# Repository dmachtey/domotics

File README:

-*- mode: org -*-

* This is another domotics project
    - it is based on Beaglebone Black
    - Its able to control up to 64 Inputs or Outputs in blocks of 4
    - I've developed a main board were is possible to plug up to 16
      4-inputs or 4-outputs boards (4 GPIOs). All of them are
      optocoupled.
      - I've already developed a 4-relays board and 4-transistors
        board wich can control lights intensity by PWM and also
        4-imputs board
    - The power board can be connected to a battery and detect a mains
      failure
    - It's already able to comunicate with Openhab, an android and ios
      application
    - It's in production now since April 8th 2016 in my home
    - There is also 2 more slots with 3 and 4 analogs inputs, I'm
      planing to sense the battery level and natural light level.
    - Into one of the 16 slots I'm planing to connect some DS18B20 (up
      to 10 can be connected to one gpio) to sense the rooms
      temperatures.

* This is my first project to be published
  I'm trying to sort thins out to make them easier to understan

  I will re-write some of c++ objects to make them clear to understand

* This is what is now running
  - A full functional project is in production at my home have a look
    at the pictures folder
  - Now I'm controlling 5 PWM circuits for lights
  - I've also 5 inputs
  - All outputs are controlled by Openhab web application from LAN/WAN

* How to test this project
  - Get a Beagle bone black with Linux running
  - do :: apt-get install build-essential
  - do :: apt-get install linux-image-3.8.13-bone68 device-tree-compiler
    - to be able to compile new capes, they are needed to manage GPIOs
  - compile the cape /domotics/capes/half-in-half-pru.dts
    - copy the compiled code to /lib/firmware/
  - get yours electronics ready and connected to one of the gpio used
    on "on-production/test-pwm.cpp" like "GPIO 27"
  - Connect and input switch at "GPIO 4"
  - copy the contemns of "/domotics/on-production" to /pru2 at BBB
  - run /pru2/start.sh
  - Your led should get PWM controlled with the switch

  - Optional:
    If you want to run it with openhab for remote controll
    - Install libc-ares-dev uuid-dev libwrap0-dev libssl-dev needed by
      mosquitto library
    - Install mosquitto it can be downloaded here: http://mosquitto.org/download/
  - Install openhab, instructions at it's site: http://openhab.org/
    - copy /domotics/root/* to "/" at BBB
  - Install an configure your openhab to point to your BBB ip as http://BBBip:8080

* Project files
  - /domotics/docs/files-strucure.org

* Contact information
  - Damian Machtey
  - dmachtey at gmail com

* License
  The code and hardware is being released under GPL v3.

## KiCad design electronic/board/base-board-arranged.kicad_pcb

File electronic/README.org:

*Use kitcad to open the files*

* files structure and comments (should be here)

* Scripts/other programs
  - headers-cloner.py :: was used to automatically arrange the socket
       connectors
  - FreeRouting :: was used to help ruting
    - http://www.freerouting.net/fen/viewtopic.php?f=4&t=255

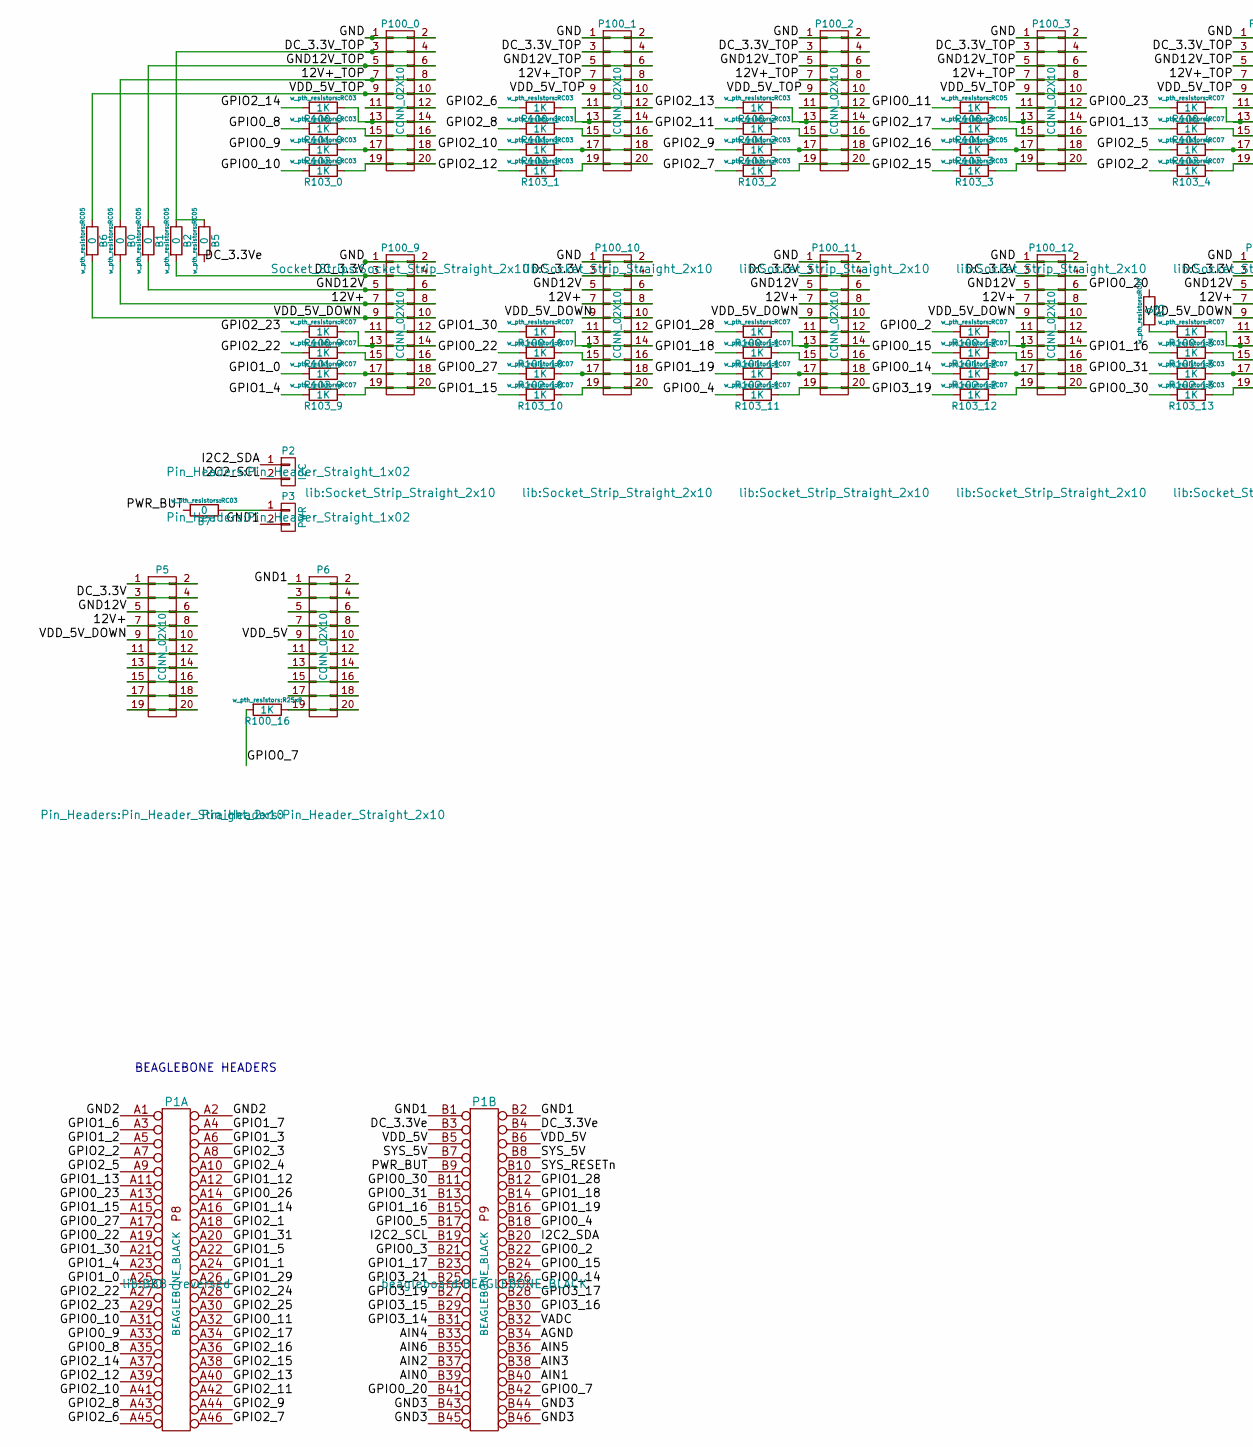
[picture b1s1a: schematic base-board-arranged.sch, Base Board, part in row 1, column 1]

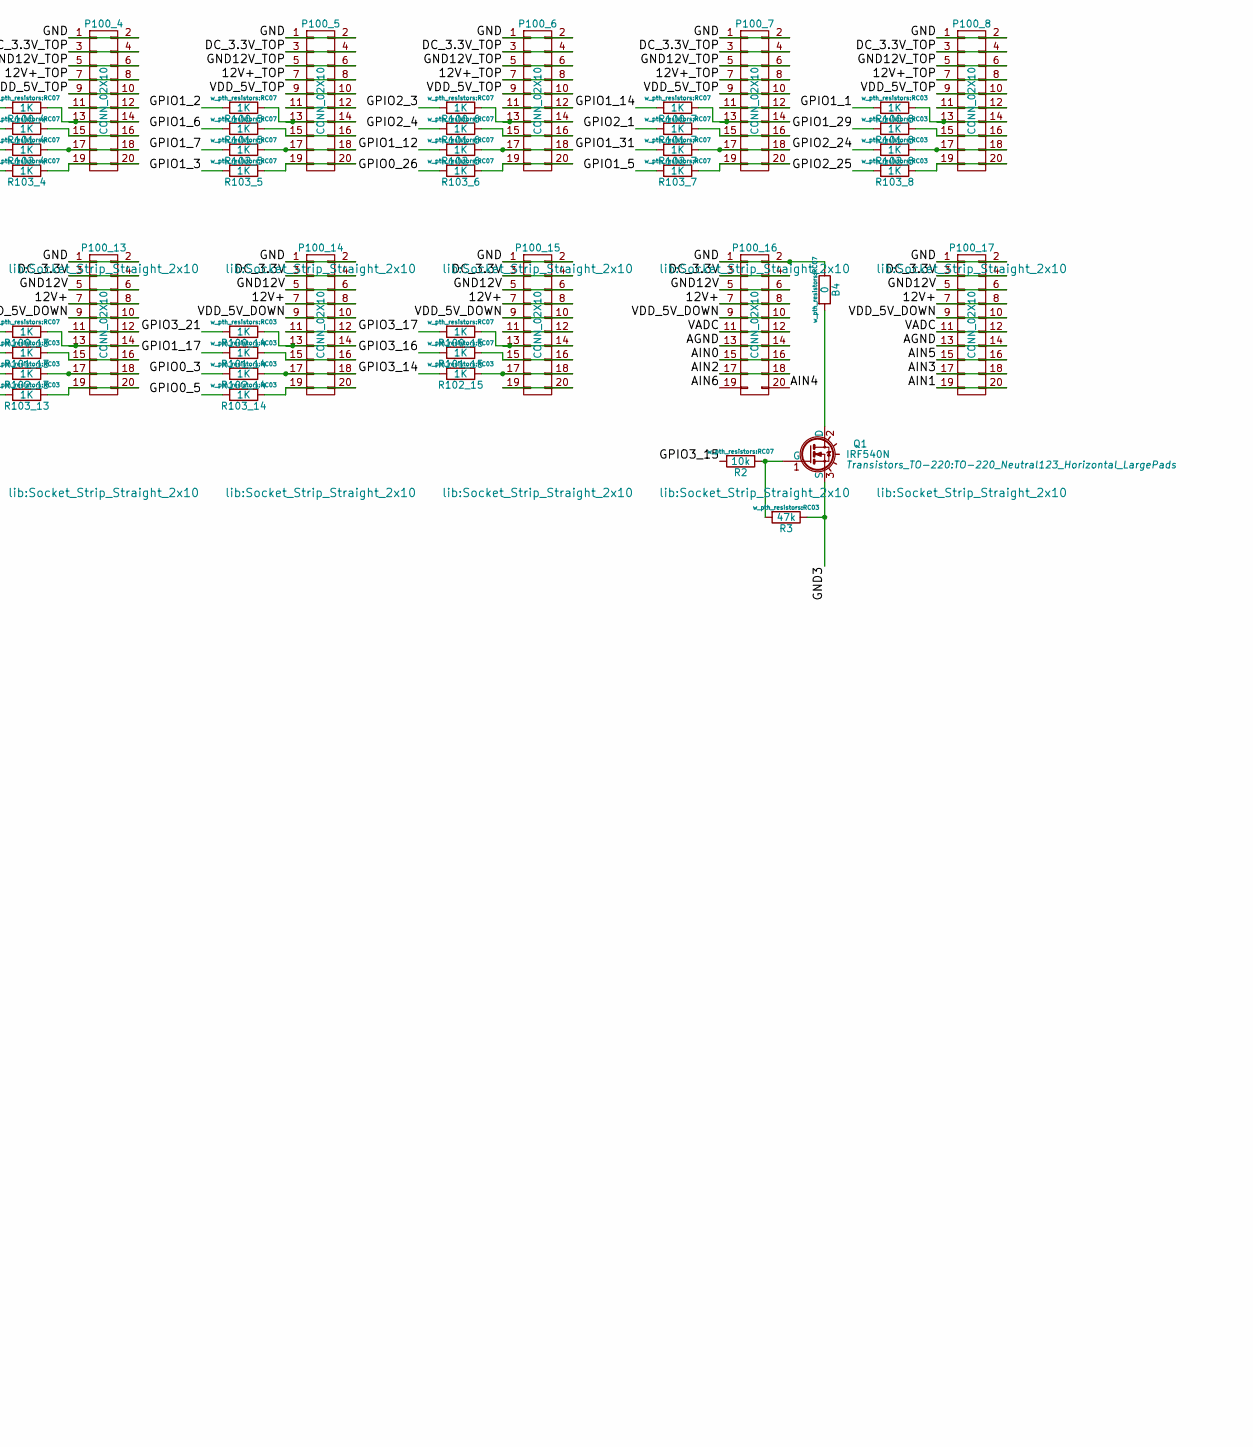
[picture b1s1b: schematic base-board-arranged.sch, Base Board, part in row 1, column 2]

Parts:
B0, B1, B2, B5, B6: 0; RC05
B3, B4: 0; RC07
B7: 0; RC03
P1: BEAGLEBONE_BLACK; BBB-reversed
P2: I2C; Pin_Header_Straight_1x02
P3: PWR; Pin_Header_Straight_1x02
P5, P6: CONN_02X10; Pin_Header_Straight_2x10
P100_0, P100_1, P100_2, P100_3, P100_4, P100_5, P100_6, P100_7, P100_8, P100_9, P100_10, P100_11, P100_12, P100_13, P100_14, P100_15, P100_16, P100_17: CONN_02X10; Socket_Strip_Straight_2x10
Q1: IRF540N; TO-220_Neutral123_Horizontal_LargePads
R2: 10k; RC07
R3: 47k; RC03
R100_0, R100_1, R100_2, R100_8, R100_14, R101_0, R101_1, R101_2, R101_8, R101_13, R101_14, R102_0, R102_1, R102_2, R102_8, R102_13, R102_14, R102_15, R103_0, R103_1, R103_2, R103_3, R103_8, R103_13, R103_14: 1K; RC03
R100_3, R101_3, R102_3: 1K; RC05
R100_4, R100_5, R100_6, R100_7, R100_9, R100_10, R100_11, R100_12, R100_13, R100_15, R101_4, R101_5, R101_6, R101_7, R101_9, R101_10, R101_11, R101_12, R101_15, R102_4, R102_5, R102_6, R102_7, R102_9, R102_10, R102_11, R102_12, R103_4, R103_5, R103_6, R103_7, R103_9, R103_10, R103_11, R103_12: 1K; RC07
R100_16: 1K; R25x8

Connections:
/12V+: B0.2, P5.7, P5.8, P100_9.7, P100_9.8, P100_10.7, P100_10.8, P100_11.7, P100_11.8, P100_12.7, P100_12.8, P100_13.7, P100_13.8, P100_14.7, P100_14.8, P100_15.7, P100_15.8, P100_16.7, P100_16.8, P100_17.7, P100_17.8
/12V+_TOP: B0.1, P100_0.7, P100_0.8, P100_1.7, P100_1.8, P100_2.7, P100_2.8, P100_3.7, P100_3.8, P100_4.7, P100_4.8, P100_5.7, P100_5.8, P100_6.7, P100_6.8, P100_7.7, P100_7.8, P100_8.7, P100_8.8
/AGND: P1.B34 (P34), P100_16.13, P100_16.14, P100_17.13, P100_17.14
/AIN0: P1.B39 (P39), P100_16.15, P100_16.16
/AIN1: P1.B40 (P40), P100_17.19, P100_17.20
/AIN2: P1.B37 (P37), P100_16.17, P100_16.18
/AIN3: P1.B38 (P38), P100_17.17, P100_17.18
/AIN4: P1.B33 (P33), P100_16.20
/AIN5: P1.B36 (P36), P100_17.15, P100_17.16
/AIN6: P1.B35 (P35), P100_16.19
/DC_3.3V: B2.2, P5.3, P5.4, P100_9.3, P100_9.4, P100_10.3, P100_10.4, P100_11.3, P100_11.4, P100_12.3, P100_12.4, P100_13.3, P100_13.4, P100_14.3, P100_14.4, P100_15.3, P100_15.4, P100_16.3, P100_16.4, P100_17.3, P100_17.4
/DC_3.3V_TOP: B2.1, B5.1, P100_0.3, P100_0.4, P100_1.3, P100_1.4, P100_2.3, P100_2.4, P100_3.3, P100_3.4, P100_4.3, P100_4.4, P100_5.3, P100_5.4, P100_6.3, P100_6.4, P100_7.3, P100_7.4, P100_8.3, P100_8.4
/DC_3.3Ve: B5.2, P1.B3, P1.B4 (P4)
/GND: B4.1, P100_0.1, P100_0.2, P100_1.1, P100_1.2, P100_2.1, P100_2.2, P100_3.1, P100_3.2, P100_4.1, P100_4.2, P100_5.1, P100_5.2, P100_6.1, P100_6.2, P100_7.1, P100_7.2, P100_8.1, P100_8.2, P100_9.1, P100_9.2, P100_10.1, P100_10.2, P100_11.1, P100_11.2, P100_12.1, P100_12.2, P100_13.1, P100_13.2, P100_14.1, P100_14.2, P100_15.1, P100_15.2, P100_16.1, P100_16.2, P100_17.1, P100_17.2
/GND1: P1.B1 (GND), P1.B2 (P2), P3.2, P6.1, P6.2
/GND2: P1.A1 (GND), P1.A2 (P2)
/GND3: P1.B43 (P43), P1.B44 (P44), P1.B45 (P45), P1.B46 (P46), Q1.3 (S), R3.1
/GND12V: B1.2, P5.5, P5.6, P100_9.5, P100_9.6, P100_10.5, P100_10.6, P100_11.5, P100_11.6, P100_12.5, P100_12.6, P100_13.5, P100_13.6, P100_14.5, P100_14.6, P100_15.5, P100_15.6, P100_16.5, P100_16.6, P100_17.5, P100_17.6
/GND12V_TOP: B1.1, P100_0.5, P100_0.6, P100_1.5, P100_1.6, P100_2.5, P100_2.6, P100_3.5, P100_3.6, P100_4.5, P100_4.6, P100_5.5, P100_5.6, P100_6.5, P100_6.6, P100_7.5, P100_7.6, P100_8.5, P100_8.6
/GPIO0_2: P1.B22 (P22), R100_12.2
/GPIO0_3: P1.B21 (P21), R102_14.2
/GPIO0_4: P1.B18 (P18), R103_11.2
/GPIO0_5: P1.B17 (P17), R103_14.2
/GPIO0_7: P1.B42 (P42), R100_16.2
/GPIO0_8: P1.A35 (P35), R101_0.2
/GPIO0_9: P1.A33 (P33), R102_0.2
/GPIO0_10: P1.A31 (P31), R103_0.2
/GPIO0_11: P1.A32 (P32), R100_3.2
/GPIO0_14: P1.B26 (P26), R102_12.2
/GPIO0_15: P1.B24 (P24), R101_12.2
/GPIO0_20: B3.1, P1.B41 (P41)
/GPIO0_22: P1.A19 (P19), R101_10.2
/GPIO0_23: P1.A13 (P13), R100_4.2
/GPIO0_26: P1.A14 (P14), R103_6.2
/GPIO0_27: P1.A17 (P17), R102_10.2
/GPIO0_30: P1.B11, R103_13.2
/GPIO0_31: P1.B13 (P13), R102_13.2
/GPIO1_0: P1.A25 (P25), R102_9.2
/GPIO1_1: P1.A24 (P24), R100_8.2
/GPIO1_2: P1.A5 (P5), R100_5.2
/GPIO1_3: P1.A6 (P6), R103_5.2
/GPIO1_4: P1.A23 (P23), R103_9.2
/GPIO1_5: P1.A22 (P22), R103_7.2
/GPIO1_6: P1.A3 (P3), R101_5.2
/GPIO1_7: P1.A4 (P4), R102_5.2
/GPIO1_12: P1.A12 (P12), R102_6.2
/GPIO1_13: P1.A11 (P11), R101_4.2
/GPIO1_14: P1.A16 (P16), R100_7.2
/GPIO1_15: P1.A15 (P15), R103_10.2
/GPIO1_16: P1.B15 (P15), R101_13.2
/GPIO1_17: P1.B23 (P23), R101_14.2
/GPIO1_18: P1.B14 (P14), R101_11.2
/GPIO1_19: P1.B16 (P16), R102_11.2
/GPIO1_28: P1.B12 (P12), R100_11.2
/GPIO1_29: P1.A26 (P26), R101_8.2
/GPIO1_30: P1.A21 (P21), R100_10.2
/GPIO1_31: P1.A20 (P20), R102_7.2
/GPIO2_1: P1.A18 (P18), R101_7.2
/GPIO2_2: P1.A7 (P7), R103_4.2
/GPIO2_3: P1.A8 (P8), R100_6.2
/GPIO2_4: P1.A10 (P10), R101_6.2
/GPIO2_5: P1.A9 (P9), R102_4.2
/GPIO2_6: P1.A45 (P45), R100_1.2
/GPIO2_7: P1.A46 (P46), R103_2.2
/GPIO2_8: P1.A43 (P43), R101_1.2
/GPIO2_9: P1.A44 (P44), R102_2.2
/GPIO2_10: P1.A41 (P41), R102_1.2
/GPIO2_11: P1.A42 (P42), R101_2.2
/GPIO2_12: P1.A39 (P39), R103_1.2
/GPIO2_13: P1.A40 (P40), R100_2.2
/GPIO2_14: P1.A37 (P37), R100_0.2
/GPIO2_15: P1.A38 (P38), R103_3.2
/GPIO2_16: P1.A36 (P36), R102_3.2
/GPIO2_17: P1.A34 (P34), R101_3.2
/GPIO2_22: P1.A27 (P27), R101_9.2
/GPIO2_23: P1.A29 (P29), R100_9.2
/GPIO2_24: P1.A28 (AP28), R102_8.2
/GPIO2_25: P1.A30 (P30), R103_8.2
/GPIO3_14: P1.B31 (P31), R102_15.2
/GPIO3_15: P1.B29 (P29), R2.2
/GPIO3_16: P1.B30 (P30), R101_15.2
/GPIO3_17: P1.B28 (AP28), R100_15.2
/GPIO3_19: P1.B27 (P27), R103_12.2
/GPIO3_21: P1.B25 (P25), R100_14.2
/I2C2_SCL: P1.B19 (P19), P2.2
/I2C2_SDA: P1.B20 (P20), P2.1
/PWR_BUT: B7.2, P1.B9 (P9)
/SYS_5V: P1.B7 (P7), P1.B8 (P8)
/SYS_RESETn: P1.B10 (P10)
/VADC: P1.B32 (P32), P100_16.11, P100_16.12, P100_17.11, P100_17.12
/VDD_5V: P1.B5 (P5), P1.B6 (P6), P6.9, P6.10
/VDD_5V_DOWN: B6.2, P5.9, P5.10, P100_9.9, P100_9.10, P100_10.9, P100_10.10, P100_11.9, P100_11.10, P100_12.9, P100_12.10, P100_13.9, P100_13.10, P100_14.9, P100_14.10, P100_15.9, P100_15.10, P100_16.9, P100_16.10, P100_17.9, P100_17.10
/VDD_5V_TOP: B6.1, P100_0.9, P100_0.10, P100_1.9, P100_1.10, P100_2.9, P100_2.10, P100_3.9, P100_3.10, P100_4.9, P100_4.10, P100_5.9, P100_5.10, P100_6.9, P100_6.10, P100_7.9, P100_7.10, P100_8.9, P100_8.10
unnamed: B3.2, R100_13.2
unnamed: B4.2, Q1.2 (D)
unnamed: B7.1, P3.1
unnamed: P5.1, P5.2
unnamed: P5.11, P5.12
unnamed: P5.13, P5.14
unnamed: P5.15, P5.16
unnamed: P5.17, P5.18
unnamed: P5.19, P5.20
unnamed: P6.3, P6.4
unnamed: P6.5, P6.6
unnamed: P6.7, P6.8
unnamed: P6.11, P6.12
unnamed: P6.13, P6.14
unnamed: P6.15, P6.16
unnamed: P6.17, P6.18
unnamed: P6.19, P6.20, R100_16.1
unnamed: P100_0.11, P100_0.12
unnamed: P100_0.13, P100_0.14, R100_0.1
unnamed: P100_0.15, P100_0.16, R101_0.1
unnamed: P100_0.17, P100_0.18, R102_0.1
unnamed: P100_0.19, P100_0.20, R103_0.1
unnamed: P100_1.11, P100_1.12
unnamed: P100_1.13, P100_1.14, R100_1.1
unnamed: P100_1.15, P100_1.16, R101_1.1
unnamed: P100_1.17, P100_1.18, R102_1.1
unnamed: P100_1.19, P100_1.20, R103_1.1
unnamed: P100_2.11, P100_2.12
unnamed: P100_2.13, P100_2.14, R100_2.1
unnamed: P100_2.15, P100_2.16, R101_2.1
unnamed: P100_2.17, P100_2.18, R102_2.1
unnamed: P100_2.19, P100_2.20, R103_2.1
unnamed: P100_3.11, P100_3.12
unnamed: P100_3.13, P100_3.14, R100_3.1
unnamed: P100_3.15, P100_3.16, R101_3.1
unnamed: P100_3.17, P100_3.18, R102_3.1
unnamed: P100_3.19, P100_3.20, R103_3.1
unnamed: P100_4.11, P100_4.12
unnamed: P100_4.13, P100_4.14, R100_4.1
unnamed: P100_4.15, P100_4.16, R101_4.1
unnamed: P100_4.17, P100_4.18, R102_4.1
unnamed: P100_4.19, P100_4.20, R103_4.1
unnamed: P100_5.11, P100_5.12
unnamed: P100_5.13, P100_5.14, R100_5.1
unnamed: P100_5.15, P100_5.16, R101_5.1
unnamed: P100_5.17, P100_5.18, R102_5.1
unnamed: P100_5.19, P100_5.20, R103_5.1
unnamed: P100_6.11, P100_6.12
unnamed: P100_6.13, P100_6.14, R100_6.1
unnamed: P100_6.15, P100_6.16, R101_6.1
unnamed: P100_6.17, P100_6.18, R102_6.1
unnamed: P100_6.19, P100_6.20, R103_6.1
unnamed: P100_7.11, P100_7.12
unnamed: P100_7.13, P100_7.14, R100_7.1
unnamed: P100_7.15, P100_7.16, R101_7.1
unnamed: P100_7.17, P100_7.18, R102_7.1
unnamed: P100_7.19, P100_7.20, R103_7.1
unnamed: P100_8.11, P100_8.12
unnamed: P100_8.13, P100_8.14, R100_8.1
unnamed: P100_8.15, P100_8.16, R101_8.1
unnamed: P100_8.17, P100_8.18, R102_8.1
unnamed: P100_8.19, P100_8.20, R103_8.1
unnamed: P100_9.11, P100_9.12
unnamed: P100_9.13, P100_9.14, R100_9.1
unnamed: P100_9.15, P100_9.16, R101_9.1
unnamed: P100_9.17, P100_9.18, R102_9.1
unnamed: P100_9.19, P100_9.20, R103_9.1
unnamed: P100_10.11, P100_10.12
unnamed: P100_10.13, P100_10.14, R100_10.1
unnamed: P100_10.15, P100_10.16, R101_10.1
unnamed: P100_10.17, P100_10.18, R102_10.1
unnamed: P100_10.19, P100_10.20, R103_10.1
unnamed: P100_11.11, P100_11.12
unnamed: P100_11.13, P100_11.14, R100_11.1
unnamed: P100_11.15, P100_11.16, R101_11.1
unnamed: P100_11.17, P100_11.18, R102_11.1
unnamed: P100_11.19, P100_11.20, R103_11.1
unnamed: P100_12.11, P100_12.12
unnamed: P100_12.13, P100_12.14, R100_12.1
unnamed: P100_12.15, P100_12.16, R101_12.1
unnamed: P100_12.17, P100_12.18, R102_12.1
unnamed: P100_12.19, P100_12.20, R103_12.1
unnamed: P100_13.11, P100_13.12
unnamed: P100_13.13, P100_13.14, R100_13.1
unnamed: P100_13.15, P100_13.16, R101_13.1
unnamed: P100_13.17, P100_13.18, R102_13.1
unnamed: P100_13.19, P100_13.20, R103_13.1
unnamed: P100_14.11, P100_14.12
unnamed: P100_14.13, P100_14.14, R100_14.1
unnamed: P100_14.15, P100_14.16, R101_14.1
unnamed: P100_14.17, P100_14.18, R102_14.1
unnamed: P100_14.19, P100_14.20, R103_14.1
unnamed: P100_15.11, P100_15.12
unnamed: P100_15.13, P100_15.14, R100_15.1
unnamed: P100_15.15, P100_15.16, R101_15.1
unnamed: P100_15.17, P100_15.18, R102_15.1
unnamed: P100_15.19, P100_15.20
unnamed: Q1.1 (G), R2.1, R3.2

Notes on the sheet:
BEAGLEBONE HEADERS

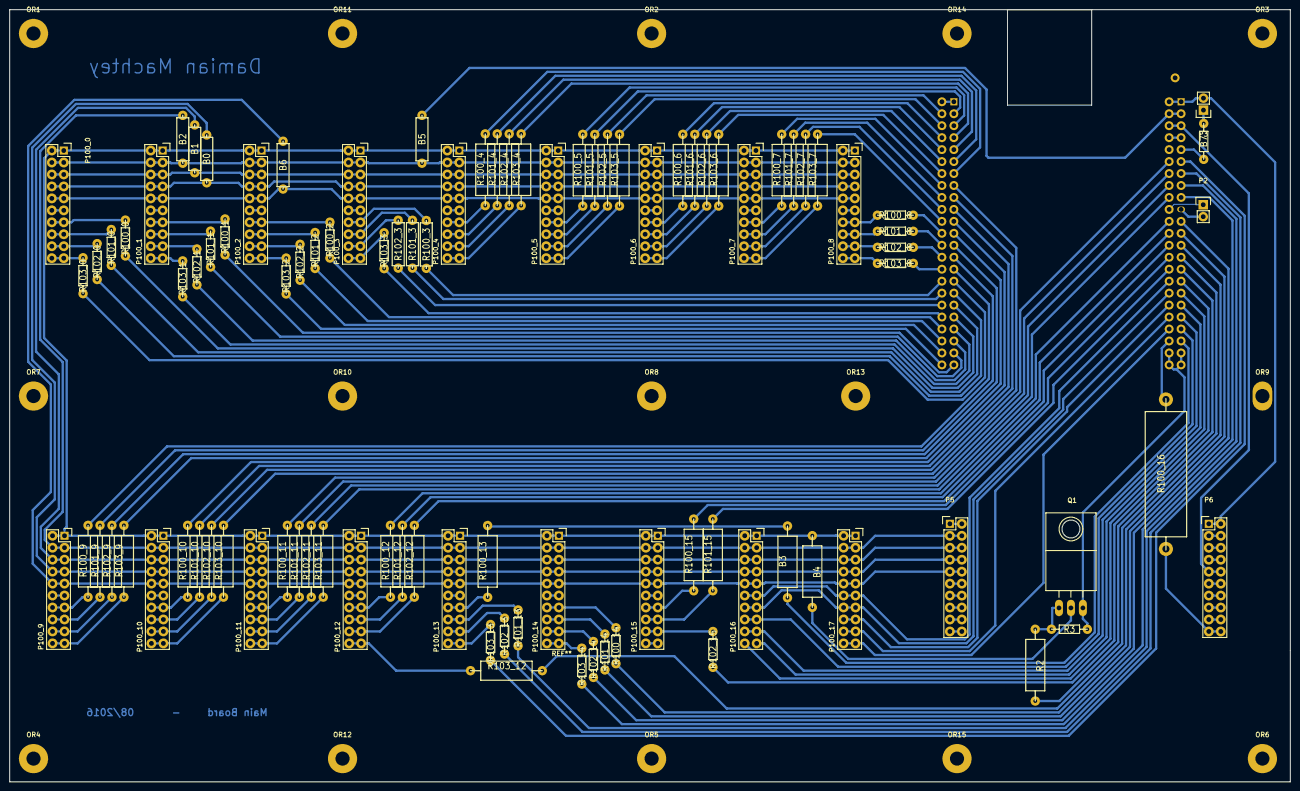
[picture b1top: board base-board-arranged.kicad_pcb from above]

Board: 2 copper layers, 272.0 x 164.0 mm, 113 parts (0 on the bottom side), 190 nets.

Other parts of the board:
OR1, OR2, OR3, OR4, OR5, OR6, OR7, OR8, OR9, OR10, OR11, OR12, OR13, OR14, OR15: Fix Hole; SolderWirePad_single_2-5mmDrill

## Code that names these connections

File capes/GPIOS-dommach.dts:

/* Filename: GPIOS-dommach.dts
*
* Description:
* Author: Damian Machtey
* Maintainer:
*
* Created: Wed Sep 21 07:56:37 2016 (-0300)
*
* Last-Updated: Fri Jun 30 16:49:44 2017 (-0300)
*           By: Damian Machtey
*     Update #: 10

* Change Log:
*

* Copyright (C) 2016 Damian Machtey

* This program is free software: you can redistribute it and/or modify
* it under the terms of the GNU General Public License as published by
* the Free Software Foundation, either version 3 of the License, or (at
* your option) any later version.
*
* This program is distributed in the hope that it will be useful, but
* WITHOUT ANY WARRANTY; without even the implied warranty of
* MERCHANTABILITY or FITNESS FOR A PARTICULAR PURPOSE.  See the GNU
* General Public License for more details.
*
* You should have received a copy of the GNU General Public License
* along with this program.  If not, see <http://www.gnu.org/licenses/>.
*/

/* Code: */

/dts-v1/;
/plugin/;

/{
    compatible = "ti,beaglebone", "ti,beaglebone-black";
    part-number = "GPIOS-dommach";
    version = "00A0";

    fragment@0 {
        target = <&am33xx_pinmux>;

        __overlay__ {
            gpios: GPIOS-dommach {
			    pinctrl-single,pins = <

                /* OUTPUT  GPIO(mode7) 0x07 pulldown, 0x17 pullup, 0x?f no pullup/down */
			    /* INPUT   GPIO(mode7) 0x27 pulldown, 0x37 pullup, 0x?f no pullup/down */
        //| Address | Mode | BBB Port | gpio number |  Slot | Order | Mode 7   | Mode  | Mode | Comment |
        //|---------+------+----------+-------------+-------+-------+----------+-------+------+---------|
                0x164  0x27  // P9_42 |           7 | Power |       | GPIO0_7  |       |      | Mains   |

                0x0D8  0x07  // P8_31 |          10 |     0 |     1 | GPIO0_10 |       |      |         |
                0x0D4  0x07  // P8_33 |           9 |     0 |     2 | GPIO0_9  |       |      |         |
                0x0D0  0x07  // P8_35 |           8 |     0 |     3 | GPIO0_8  |       |      |         |
                0x0C0  0x27  // P8_37 |          78 |     0 |     4 | GPIO2_14 |       |      |         |

                0x0B8  0x27  // P8_39 |          76 |     1 |     1 | GPIO2_12 |       |      |         |
                0x0B0  0x27  // P8_41 |          74 |     1 |     2 | GPIO2_10 |       |      |         |
                0x0A8  0x27  // P8_43 |          72 |     1 |     3 | GPIO2_8  |       |      |         |
                0x0A0  0x27  // P8_45 |          70 |     1 |     4 | GPIO2_6  |       |      |         |

                0x0A4  0x27  // P8_46 |          71 |     2 |     1 | GPIO2_7  |       |      |         |
                0x0AC  0x27  // P8_44 |          73 |     2 |     2 | GPIO2_9  |       |      |         |
                0x0B4  0x27  // P8_42 |          75 |     2 |     3 | GPIO2_11 |       |      |         |
                0x0BC  0x27  // P8_40 |          77 |     2 |     4 | GPIO2_13 |       |      |         |

                0x0C4  0x27  // P8_38 |          79 |     3 |     1 | GPIO2_15 |       |      |         |
                0x0C8  0x27  // P8_36 |          80 |     3 |     2 | GPIO2_16 |       |      |         |
                0x0CC  0x07  // P8_34 |          81 |     3 |     3 | GPIO2_17 |       |      |         |
                0x0DC  0x07  // P8_32 |          11 |     3 |     4 | GPIO0_11 |       |      |         |

                0x090  0x07  // P8_07 |          66 |     4 |     1 | GPIO2_2  |       |      |         |
                0x09c  0x07  // P8_09 |          69 |     4 |     2 | GPIO2_5  |       |      |         |
                0x034  0x07  // P8_11 |          45 |     4 |     3 | GPIO1_13 |       |      |         |
                0x024  0x07  // P8_13 |          23 |     4 |     4 | GPIO0_23 |       |      |         |

                0x00c  0x07  // P8_06 |          35 |     5 |     1 | GPIO1_3  |       |      |         |
                0x01c  0x07  // P8_04 |          39 |     5 |     2 | GPIO1_7  |       |      |         |
                0x018  0x07  // P8_03 |          38 |     5 |     3 | GPIO1_6  |       |      |         |
                0x008  0x07  // P8_05 |          34 |     5 |     4 | GPIO1_2  |       |      |         |

                0x028  0x07  // P8_14 |          26 |     6 |     1 | GPIO0_26 |       |      |         |
                0x030  0x07  // P8_12 |          44 |     6 |     2 | GPIO1_12 |       |      |         |
                0x098  0x07  // P8_10 |          68 |     6 |     3 | GPIO2_4  |       |      |         |
                0x094  0x07  // P8_08 |          67 |     6 |     4 | GPIO2_3  |       |      |         |

                0x014  0x07  // P8_22 |          37 |     7 |     1 | GPIO1_5  |       |      |         |
                0x084  0x07  // P8_20 |          63 |     7 |     2 | GPIO1_31 | UART4 |      |         |
                0x08c  0x07  // P8_18 |          65 |     7 |     3 | GPIO2_1  |       |      |         |
                0x038  0x07  // P8_16 |          46 |     7 |     4 | GPIO1_14 |       |      |         |

                0x0EC  0x07  // P8_30 |          89 |     8 |     1 | GPIO2_25 |       |      |         |
                0x0E8  0x07  // P8_28 |          88 |     8 |     2 | GPIO2_24 |       |      |         |
                0x07c  0x07  // P8_26 |          61 |     8 |     3 | GPIO1_29 |       |      |         |
                0x004  0x07  // P8_24 |          33 |     8 |     4 | GPIO1_1  |       |      |         |

                0x010  0x07  // P8_23 |          36 |     9 |     1 | GPIO1_4  |       |      |         |
                0x000  0x07  // P8_25 |          32 |     9 |     2 | GPIO1_0  |       |      |         |
                0x0E0  0x07  // P8_27 |          86 |     9 |     3 | GPIO2_22 |       |      |         |
                0x0E4  0x07  // P8_29 |          87 |     9 |     4 | GPIO2_23 |       |      |         |

                0x03c  0x07  // P8_15 |          47 |    10 |     1 | GPIO1_15 |       |      |         |
                0x02c  0x07  // P8_17 |          27 |    10 |     2 | GPIO0_27 |       |      |         |
                0x020  0x07  // P8_19 |          22 |    10 |     3 | GPIO0_22 |       |      |         |
                0x080  0x07  // P8_21 |          62 |    10 |     4 | GPIO1_30 | UART4 |      |         |

                0x158  0x27  // P9_18 |           4 |    11 |     1 | GPIO0_4  | I2C1  |      |         |
                0x04c  0x27  // P9_16 |          51 |    11 |     2 | GPIO1_19 |       |      |         |
                0x048  0x27  // P9_14 |          50 |    11 |     3 | GPIO1_18 |       |      |         |
                0x078  0x27  // P9_12 |          60 |    11 |     4 | GPIO1_28 |       |      |         |

                0x1a4  0x27  // P9_27 |         115 |    12 |     1 | GPIO3_1  |       |      |         |
                0x180  0x27  // P9_26 |          14 |    12 |     2 | GPIO0_14 | UART1 | I2C1 |         |
                0x184  0x27  // P9_24 |          15 |    12 |     3 | GPIO0_15 | UART1 | I2C1 |         |
                0x150  0x27  // P9_22 |           2 |    12 |     4 | GPIO0_2  | UART2 | I2C2 |         |

                0x070  0x27  // P9_11 |          30 |    13 |     1 | GPIO0_30 |       |      |         |
                0x074  0x27  // P9_13 |          31 |    13 |     2 | GPIO0_31 |       |      |         |
                0x040  0x27  // P9_15 |          48 |    13 |     3 | GPIO1_16 |       |      |         |
                0x1b4  0x27  // P9_41 |          20 |    13 |     4 | GPIO0_20 |       |      |         |

                0x15c  0x27  // P9_17 |           5 |    14 |     1 | GPIO0_5  | I2C1  |      |         |
                0x154  0x27  // P9_21 |           3 |    14 |     2 | GPIO0_3  | UART2 | I2C2 |         |
                0x044  0x27  // P9_23 |          49 |    14 |     3 | GPIO1_17 |       |      |         |
                0x1ac  0x27  // P9_25 |         117 |    14 |     4 | GPIO3_21 |       |      |         |

                0x194  0x27  // P9_29 |         111 |    15 |     1 | GPIO3_15 | SPI   |      |Board En |
                0x190  0x27  // P9_31 |         110 |    15 |     2 | GPIO3_14 | SPI   |      |         |
                0x198  0x27  // P9_30 |         112 |    15 |     3 | GPIO3_16 | SPI   |      |         |
                0x19c  0x27  // P9_28 |         113 |    15 |     4 | GPIO3_17 | SPI   |      |         |
			    >;
		    };
        };
    };

    fragment@1 {
		target = <&ocp>;
		__overlay__ {
			gpio_helper {
				compatible = "gpio-of-helper";
				status = "okay";
				pinctrl-names = "default";
				pinctrl-0 = <&gpios>;
			};
		};
	};
};

/* GPIOS-dommach.dts ends here */

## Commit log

2016-07-17 * .gitignore:
2016-07-17 still initial
2016-07-17 Initial commint
2016-07-17 Init commint
2016-07-18 Inital commit
2016-07-18 capes makefile added
2016-07-20 headers
2016-07-22 going to new objects
2016-07-23 Very last running version
2016-07-24 New ideas
2016-07-24 Somo ideas
2016-07-24 Some ideas
2016-07-28 advancing with new objects, just testing
2016-07-28 lapse and coil now seem to be working
2016-07-29 New classes in the way
2016-07-29 some arrangements
2016-07-29 going on with the new clases
2016-07-29 Some grammatical corrections
2016-07-29 grammar
2016-07-30 clases
2016-07-30 Config files
2016-07-30 Debug messages added
2016-07-30 Unneeded library removed
2016-07-30 Removing old c style code
2016-07-31 going
2016-08-02 New pru macros, program was split
2016-08-03 temperature added
2016-08-06 New pru-loader class, some macros
2016-08-09 Pru_loader tested, Mem CPY on pruss
2016-08-09 main.cpp populated
2016-08-09 Makefile, a correction on pwm.p
2016-08-10 running now
2016-08-14 going on/off threaded, almost done
2016-08-14 gitignore
2016-08-14 Some openhab cfg
2016-08-15 Threads corrected
2016-08-16 Door opener added
2016-08-20 Inform the user about timing out
2016-08-24 Some hw, +others
2016-08-24 Cape makefile
2016-08-24 Cape mod
2016-08-24 renamed
2016-08-25 Main Board
2016-08-25 Readme
2016-08-25 Small mod
2016-08-25 gitmore
2016-08-25 gitgnore
2016-08-26 Main board, IOs gated
2016-09-06 Todo
2016-09-12 3d models - enclosure them
2016-10-09 Some photos
2016-11-10 Named ios, as Slot, Port
2017-06-30 License statement
2017-06-30 License statement error corrected
